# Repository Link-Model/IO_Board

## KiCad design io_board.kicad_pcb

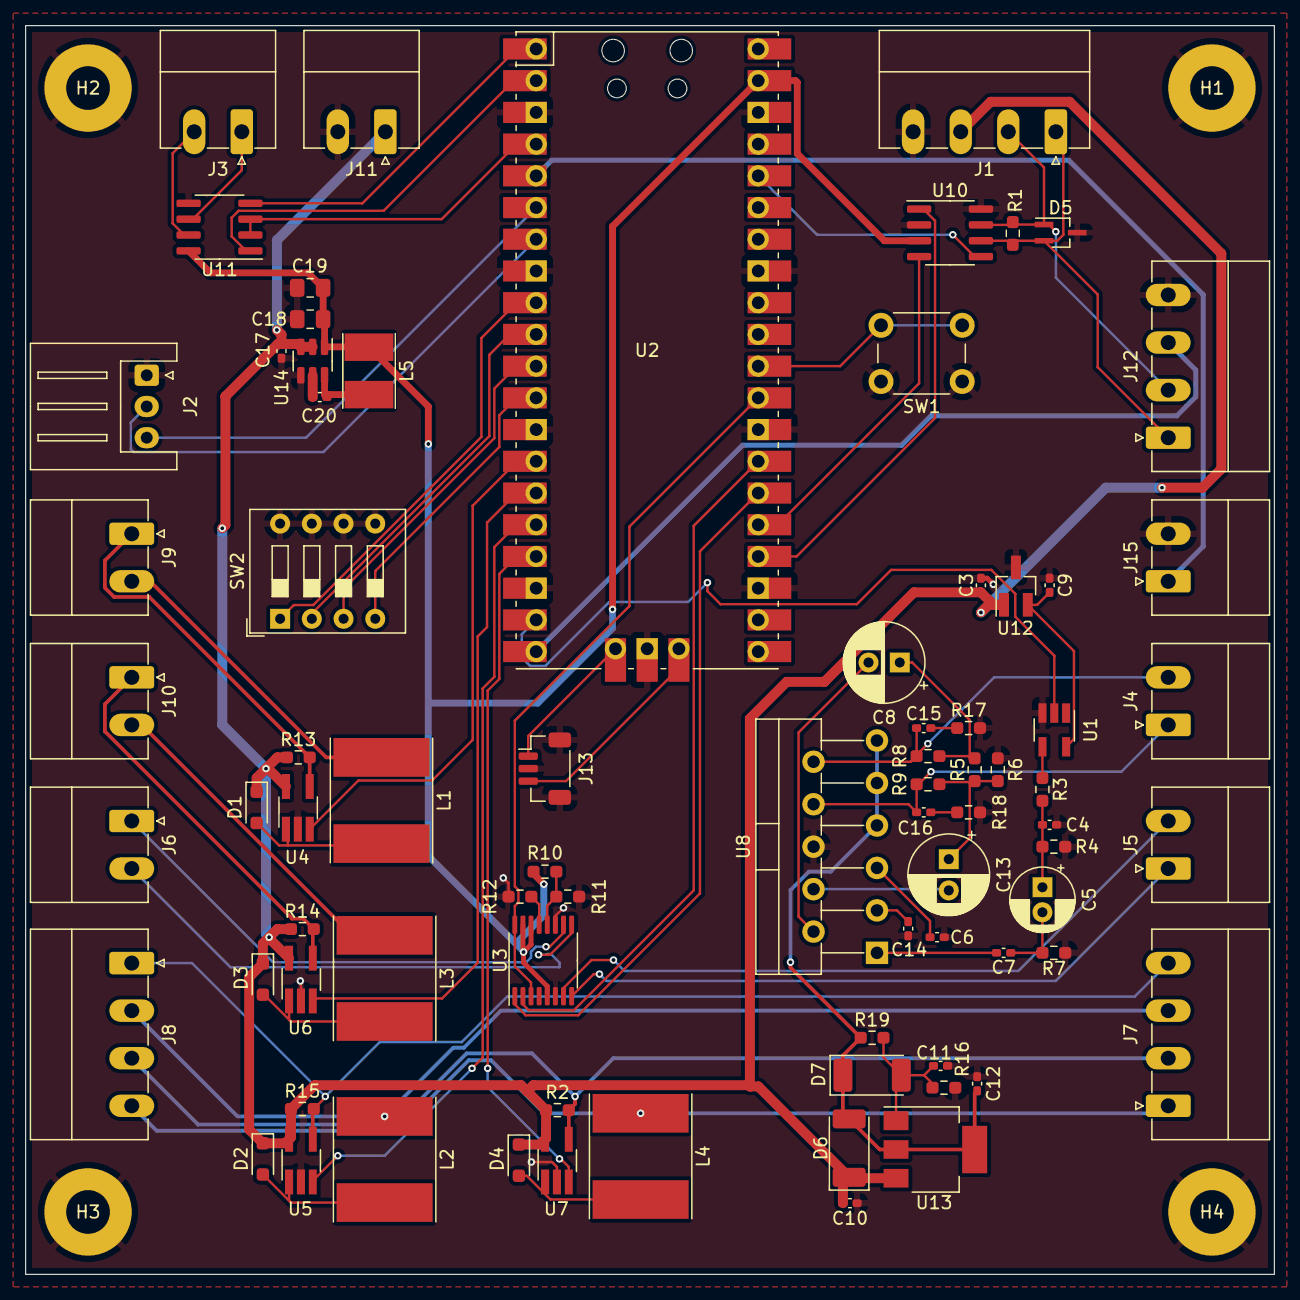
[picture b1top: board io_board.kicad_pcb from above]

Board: 2 copper layers, 100.0 x 100.0 mm, 82 parts (0 on the bottom side), 69 nets.

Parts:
C3, C11, C12: 1uF; C_0402_1005Metric_Pad0.74x0.62mm_HandSolder
C4, C20: 100nF; C_0402_1005Metric_Pad0.74x0.62mm_HandSolder
C5: 47uF; CP_Radial_D5.0mm_P2.00mm
C6, C7: 2.2uF; C_0402_1005Metric_Pad0.74x0.62mm_HandSolder
C8, C13: 220uF; CP_Radial_D6.3mm_P2.50mm
C9, C14, C17: 10uF; C_0402_1005Metric_Pad0.74x0.62mm_HandSolder
C10, C15, C16: 0.1uF; C_0402_1005Metric_Pad0.74x0.62mm_HandSolder
C18, C19: 22uF; C_0805_2012Metric_Pad1.18x1.45mm_HandSolder
D1, D2, D3, D4: SD103AWS; D_SOD-323_HandSoldering
D5: PESD1CAN; SOT-323_SC-70_Handsoldering
D6, D7: M7; D_2010_5025Metric_Pad1.52x2.65mm_HandSolder
H1, H2, H3, H4: Hole; MountingHole_3.5mm_Pad
J1, J7, J8, J12: TBP02R1-381-04; PhoenixContact_MC_1,5_4-G-3.81_1x04_P3.81mm_Horizontal
J2: 25SH-B-03-TR; JST_XH_S3B-XH-A_1x03_P2.50mm_Horizontal
J3, J4, J5, J6, J9, J10, J11, J15: TBP02R1-381-02; PhoenixContact_MC_1,5_2-G-3.81_1x02_P3.81mm_Horizontal
J13: CI1103M1VR0; JST_SH_BM03B-SRSS-TB_1x03-1MP_P1.00mm_Vertical
L1, L2, L3, L4: 100uH; L_Taiyo-Yuden_NR-80xx_HandSoldering
L5: 4.7uH; L_Taiyo-Yuden_NR-40xx_HandSoldering
R1, R7: 1.8k; R_0603_1608Metric_Pad0.98x0.95mm_HandSolder
R2, R13, R14, R15: 0.1; R_0603_1608Metric_Pad0.98x0.95mm_HandSolder
R3: 220; R_0603_1608Metric_Pad0.98x0.95mm_HandSolder
R4: 100; R_0603_1608Metric_Pad0.98x0.95mm_HandSolder
R5, R6: 12; R_0603_1608Metric_Pad0.98x0.95mm_HandSolder
R8: 1k; R_0603_1608Metric_Pad0.98x0.95mm_HandSolder
R9: 2k; R_0603_1608Metric_Pad0.98x0.95mm_HandSolder
R10, R11: R_Small; R_0603_1608Metric_Pad0.98x0.95mm_HandSolder
R12: 47k; R_0603_1608Metric_Pad0.98x0.95mm_HandSolder
R16: 3.3k; R_0603_1608Metric_Pad0.98x0.95mm_HandSolder
R17, R18: 1; R_0603_1608Metric_Pad0.98x0.95mm_HandSolder
R19: 240; R_0603_1608Metric_Pad0.98x0.95mm_HandSolder
SW1: SW_Push; SW_PUSH_6mm
SW2: SW_DIP_x04; SW_DIP_SPSTx04_Slide_9.78x12.34mm_W7.62mm_P2.54mm
U1: SN74LVC1G14DBV; SOT-23-5_HandSoldering
U2: Pico; RPi_Pico_SMD_TH_no_labels
U3: TC78H660FNG; TSSOP-16_4.4x5mm_P0.65mm
U4, U5, U6, U7: AL8861; TSOT-23-5_HandSoldering
U8: TDA2005; TO-220-11_P3.4x5.08mm_StaggerOdd_Lead4.85mm_Vertical
U10: TJA1051T-3; SOIC-8_3.9x4.9mm_P1.27mm
U11: THVD1500; SOIC-8_3.9x4.9mm_P1.27mm
U12: AP7375-33SA; SOT-23_Handsoldering
U13: LM317_SOT-223; SOT-223-3_TabPin2
U14: AP63205WU; TSOT-23-6

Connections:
3V3: U2.36 (3V3), U10.5 (VIO)
5V: C18.1, C19.1, L5.2, R10.2, U2.39 (VSYS), U3.5 (VM), U3.14 (STBY), U3.15 (MODE/ERR), U10.3 (VCC), U11.8 (VCC), U14.1 (FB)
24V: C3.1, C10.1, C17.1, D1.1 (K), D2.1 (K), D3.1 (K), D4.1 (K), D6.1 (K), J1.3, J11.1, R2.1, R13.1, R14.1, R15.1, U4.5 (VIN), U5.5 (VIN), U6.5 (VIN), U7.5 (VIN), U12.1 (VI), U13.3 (VI), U14.2 (EN), U14.3 (IN)
/AUDIO_PWM: U1.2, U2.19 (GPIO14)
/Audio/AUDIO_3V3: C9.1, U1.5 (VCC), U12.2 (VO)
/Audio/SPKR+: C15.1, J4.2, R8.2, U8.10
/Audio/SPKR-: C16.1, J4.1, R9.2, U8.8
/Audio/V_AMP: C12.1, D6.2 (A), D7.1 (K), R19.1, U8.7 (BOOT), U8.9 (V+), U8.11 (BOOT), U13.2 (VO)
/CAN_H: D5.1 (A1), J1.2, J12.2, R1.1, U10.7 (CANH)
/CAN_L: D5.2 (A2), J1.1, J12.1, R1.2, U10.6 (CANL)
/CAN_RX: U2.25 (GPIO19), U10.4 (RXD)
/CAN_TX: U2.24 (GPIO18), U10.1 (TXD)
/Communication/MODBUS_A: J3.1, U11.6 (A)
/Communication/MODBUS_B: J3.2, U11.7 (B)
/DIP0: SW2.1, U2.9 (GPIO6)
/DIP1: SW2.2, U2.10 (GPIO7)
/DIP2: SW2.3, U2.11 (GPIO8)
/DIP3: SW2.4, U2.12 (GPIO9)
/DOOR_DIR: U2.29 (GPIO22), U3.3 (IN1A/Phase_A), U3.16 (IN2A/Phase_B)
/DOOR_ENA: U2.26 (GPIO20), U3.1 (IN1B/Enable_A)
/DOOR_ENB: U2.27 (GPIO21), U3.2 (IN2B/Enable_B)
/END_SENSE: J12.3, U2.20 (GPIO15)
/INVERTER_RX: J2.2, U2.7 (GPIO5)
/INVERTER_TX: J2.3, U2.6 (GPIO4)
/LED0: U2.14 (GPIO10), U4.3 (ADJ)
/LED0_AN: J9.1, R13.2, U4.4 (ISENSE)
/LED0_CAT: J9.2, L1.1
/LED1: U2.15 (GPIO11), U6.3 (ADJ)
/LED1_AN: J10.1, R14.2, U6.4 (ISENSE)
/LED1_CAT: J10.2, L3.1
/LED2: U2.16 (GPIO12), U5.3 (ADJ)
/LED2_AN: J7.4, J8.1, R15.2, U5.4 (ISENSE)
/LED2_CAT: J7.3, J8.2, L2.1
/LED3: U2.17 (GPIO13), U7.3 (ADJ)
/LED3_AN: J7.2, J8.3, R2.2, U7.4 (ISENSE)
/LED3_CAT: J7.1, J8.4, L4.1
/MODBUS_EN: U2.4 (GPIO2), U11.2 (~RE), U11.3 (DE)
/MODBUS_RX: U2.2 (GPIO1), U11.1 (RO)
/MODBUS_TX: U2.1 (GPIO0), U11.4 (DI)
/Motor/DOOR_A+: J5.2, U3.7 (OUT_A+)
/Motor/DOOR_A-: J5.1, U3.8 (OUT_A-)
/Motor/DOOR_B+: J6.1, U3.10 (OUT_B+)
/Motor/DOOR_B-: J6.2, U3.9 (OUT_B-)
/RESET: SW1.2, U2.30 (RUN)
/SPEED: J15.1, U2.5 (GPIO3)
/SWCLK: J13.1, U2.41 (SWCLK)
/SWDIO: J13.3, U2.43 (SWDIO)
GND: C3.2, C4.2, C6.2, C9.2, C10.2, C11.2, C12.2, C14.1, C17.2, C18.2, C19.2, D5.3 (common), H1.1, H2.1, H3.1, H4.1, J1.4, J2.1, J11.2, J12.4, J13.2, J13.MP (MountPin), J15.2, R4.2, R6.1, R7.2, R11.2, R12.2, R16.2, R17.2, R18.2, SW1.1, SW2.5, SW2.6, SW2.7, SW2.8, U1.3 (GND), U2.3 (GND), U2.8 (GND), U2.13 (GND), U2.18 (GND), U2.23 (GND), U2.28 (GND), U2.33 (AGND), U2.38 (GND), U2.42 (GND), U3.4 (AGND), U3.6 (PGND_A), U3.11 (PGND_B), U4.2 (GND), U5.2 (GND), U6.2 (GND), U7.2 (GND), U8.6 (GND), U10.2 (GND), U10.8 (S), U11.5 (GND), U12.3 (GND), U14.4 (GND)
unnamed: C4.1, C5.1, R3.2, R4.1
unnamed: C5.2, C7.1, R7.1
unnamed: C8.1, R5.2, R8.1
unnamed: C13.1, R5.1, R6.2, R9.1
unnamed: C15.2, R17.1
unnamed: C16.2, R18.1
unnamed: D1.2 (A), L1.2, U4.1 (LX)
unnamed: D2.2 (A), L2.2, U5.1 (LX)
unnamed: D3.2 (A), L3.2, U6.1 (LX)
unnamed: D4.2 (A), L4.2, U7.1 (LX)
unnamed: C11.1, D7.2 (A), R16.1, R19.2, U13.1 (ADJ)
unnamed: R3.1, U1.4
unnamed: R12.1, U3.13 (OSCM)
unnamed: R10.1, R11.1, U3.12 (VREF)
unnamed: C7.2, U8.1 (+)
unnamed: C8.2, U8.2 (-)
unnamed: C14.2, U8.3 (SVRR)
unnamed: C6.1, U8.5 (+)
unnamed: C13.2, U8.4 (-)
unnamed: C20.2, L5.1, U14.6 (BST)
unnamed: C20.1, U14.5 (SW)

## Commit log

2023-08-10 removing an old file
2023-08-12 added a reset button for the rp2040
2023-08-12 removed the mcp2515 can controller because I can use the can2040 library instead
